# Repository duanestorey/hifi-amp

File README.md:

# hifi-amp
A hi-fi 4-channel amplifier with active-crossovers and room correction

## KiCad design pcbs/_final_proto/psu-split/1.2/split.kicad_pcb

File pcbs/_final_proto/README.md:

## Next Updates

* Opamp voltage regulator has enable pin - can use that to kill the rails instead of a relay on split board
* Change vinyl to Muffy
* See if we can move relay for LM3886 rails somewhere else
* Add LPF to opamp power supply caps, possibly digital too

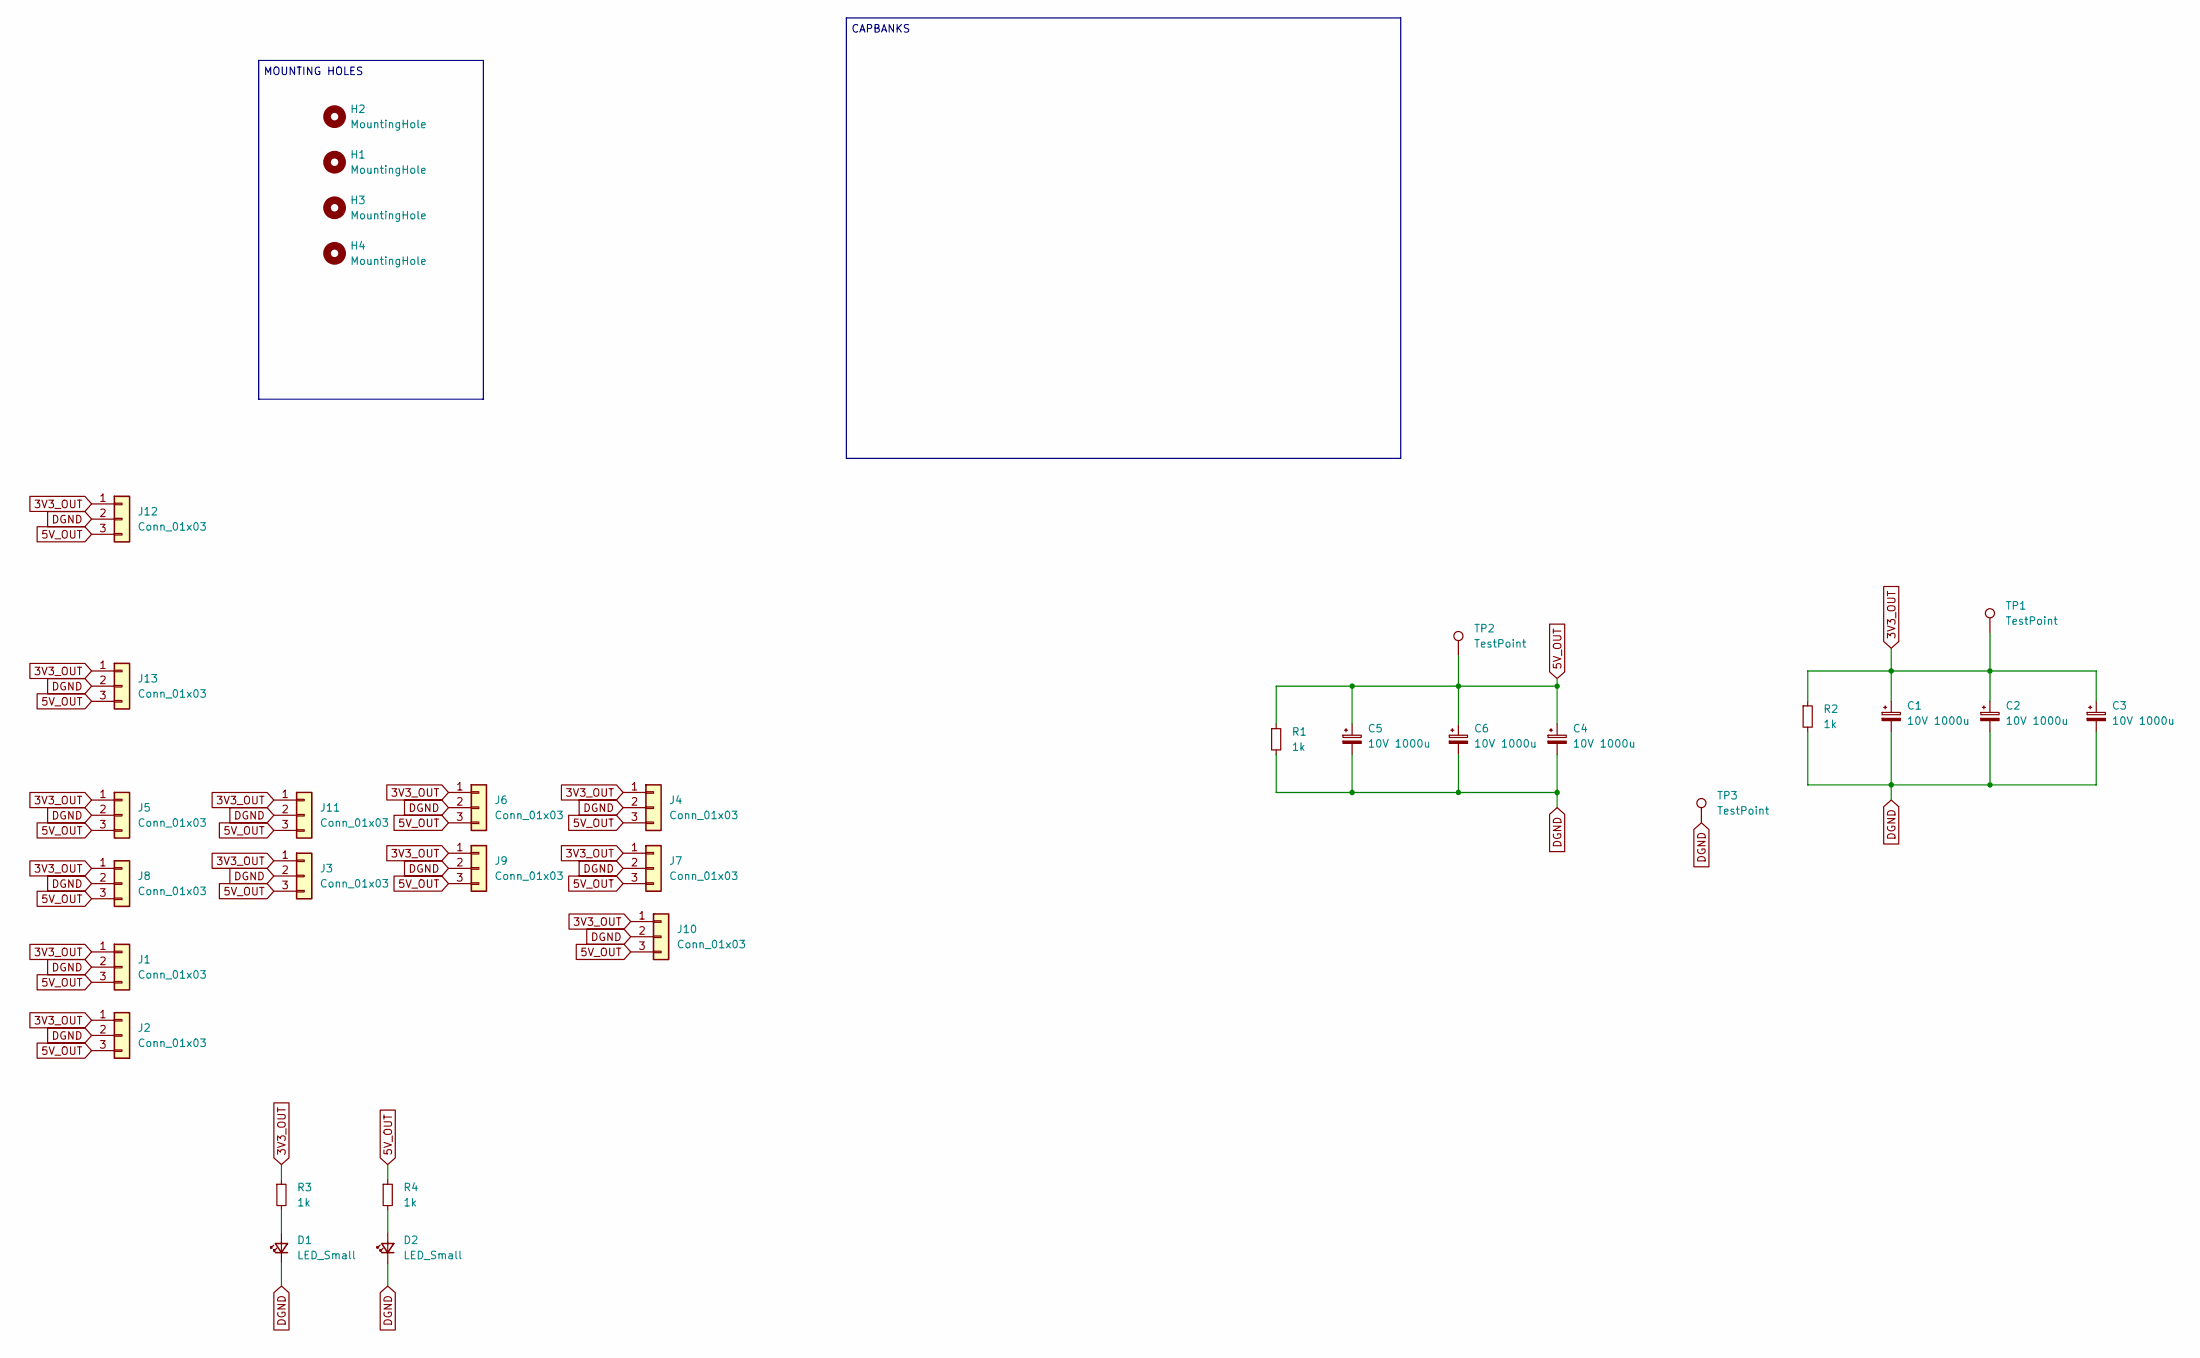
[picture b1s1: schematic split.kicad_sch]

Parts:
C1, C2, C3, C4, C5, C6: 10V 1000u; CP_Elec_10x10
D1, D2: LED_Small; LED_0805_2012Metric_Pad_HandSolder_Duane
H1, H2, H3, H4: MountingHole; MountingHole_3.2mm_M3_DIN965_Pad_TopBottom
J1, J2, J3, J4, J5, J6, J7, J8, J9, J10, J11, J13: Conn_01x03; JST_PH_B3B-PH-K_1x03_P2.00mm_Vertical
J12: Conn_01x03; JST_VH_B3P-VH-B_1x03_P3.96mm_Vertical_Duane
R1, R2, R3, R4: 1k; R_0805_2012Metric_Pad1.20x1.40mm_HandSolder_Duane
TP1, TP2, TP3: TestPoint; TestPoint_THTPad_2.5x2.5mm_Drill1.2mm

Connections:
3V3_OUT: C1.1, C2.1, C3.1, J1.1, J2.1, J3.1, J4.1, J5.1, J6.1, J7.1, J8.1, J9.1, J10.1, J11.1, J12.1, J13.1, R2.1, R3.1, TP1.1
5V_OUT: C4.1, C5.1, C6.1, J1.3, J2.3, J3.3, J4.3, J5.3, J6.3, J7.3, J8.3, J9.3, J10.3, J11.3, J12.3, J13.3, R1.1, R4.1, TP2.1
DGND: C1.2, C2.2, C3.2, C4.2, C5.2, C6.2, D1.1 (K), D2.1 (K), J1.2, J2.2, J3.2, J4.2, J5.2, J6.2, J7.2, J8.2, J9.2, J10.2, J11.2, J12.2, J13.2, R1.2, R2.2, TP3.1
unnamed: D1.2 (A), R3.2
unnamed: D2.2 (A), R4.2

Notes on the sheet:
MOUNTING HOLES
CAPBANKS

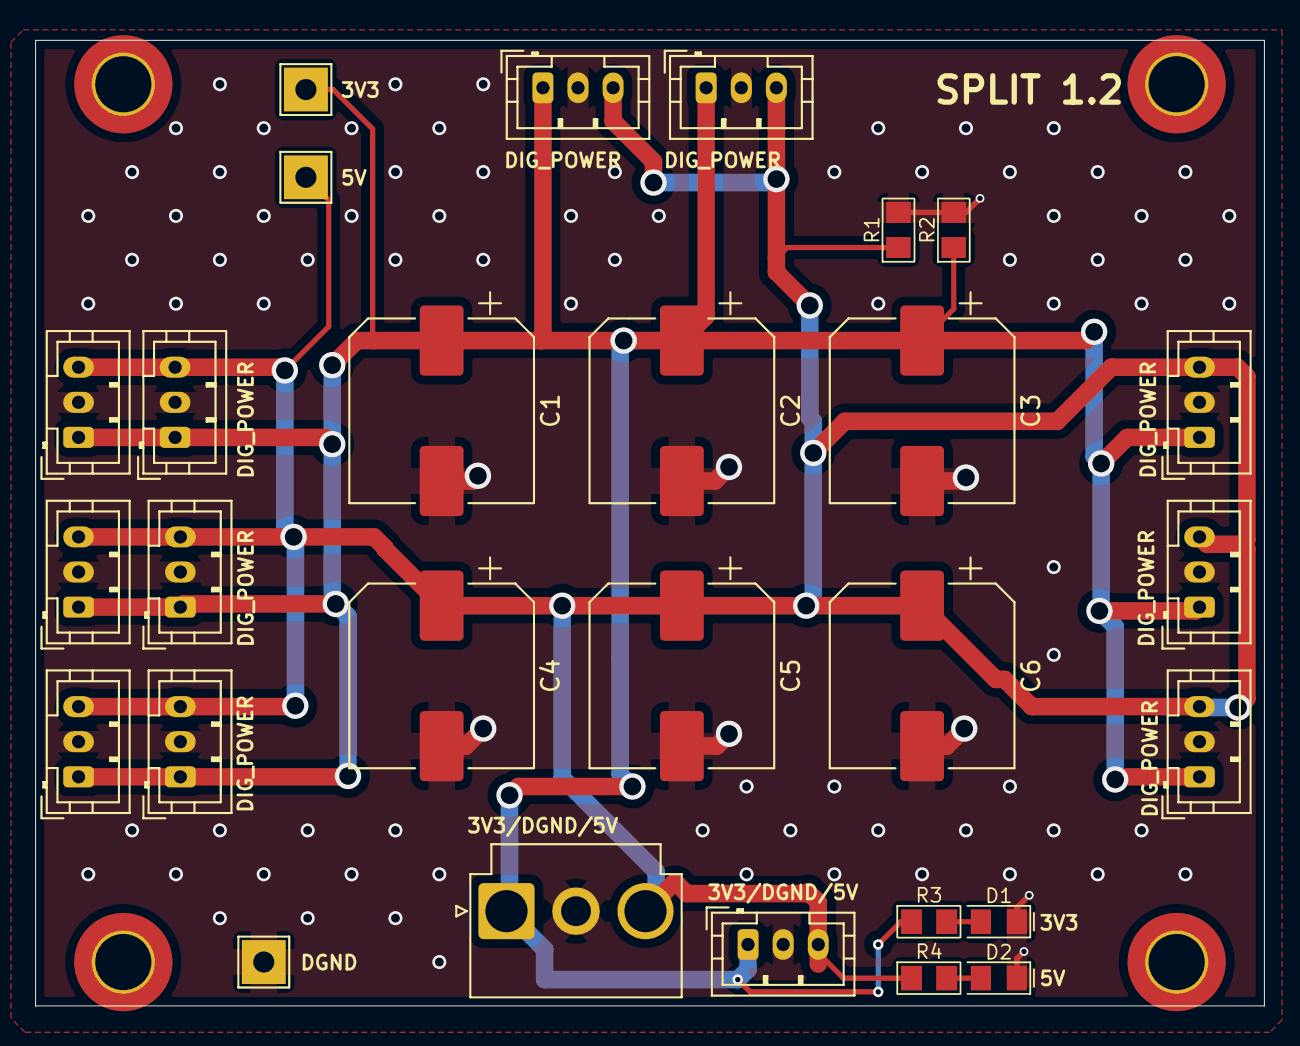
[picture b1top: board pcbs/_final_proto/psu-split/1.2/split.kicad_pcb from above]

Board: 2 copper layers, 70.0 x 55.0 mm, 32 parts (0 on the bottom side), 5 nets.

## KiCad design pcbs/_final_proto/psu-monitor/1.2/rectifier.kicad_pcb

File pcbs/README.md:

## Printed Circuit Boards

These are all the associated PCBs for the amplifier project.  They were all created in Kicad, and the boards optimized for production via JLCPCB.

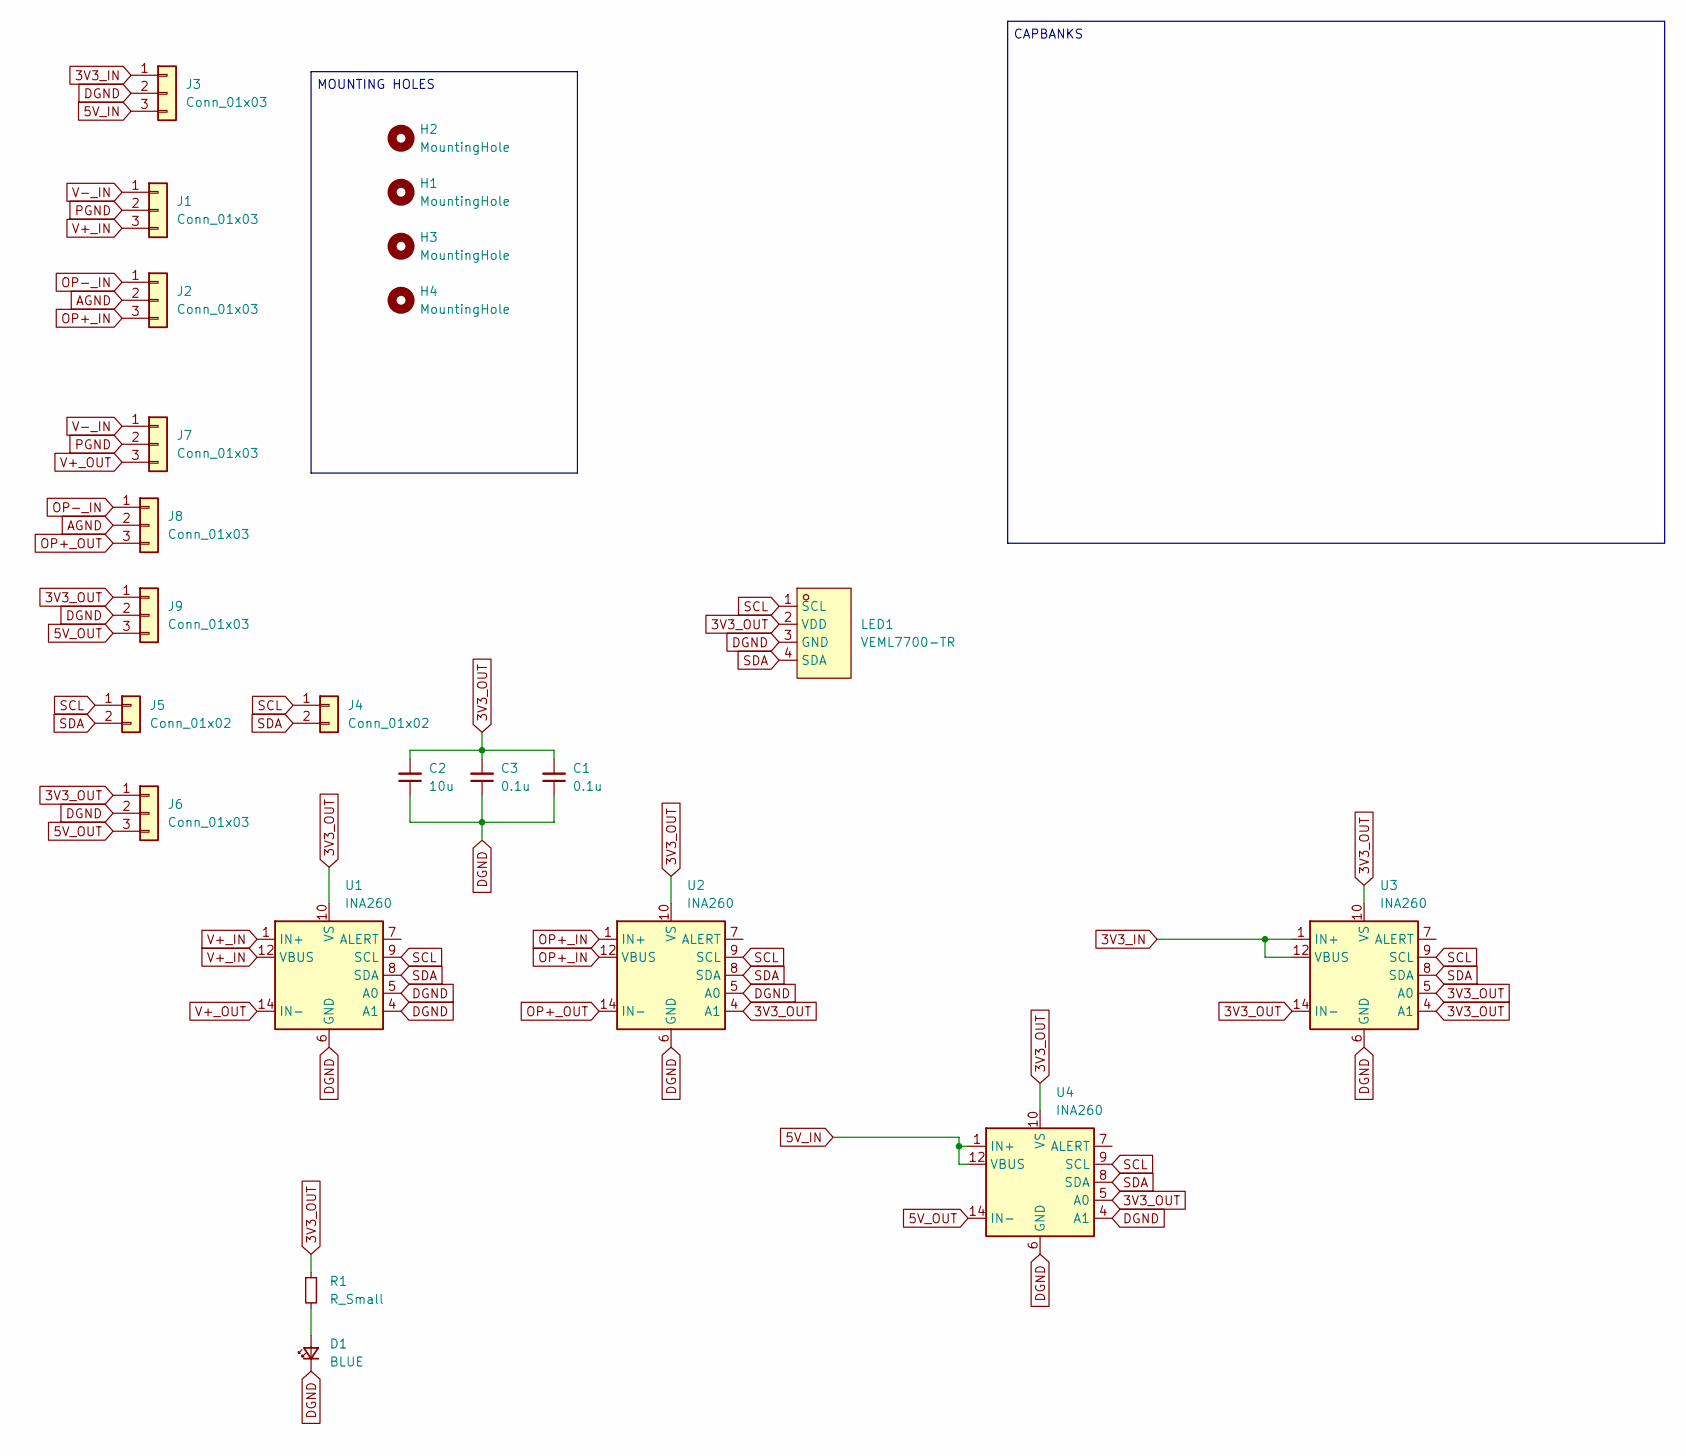
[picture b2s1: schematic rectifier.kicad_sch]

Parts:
C1, C3: 0.1u; C_0805_2012Metric_Pad1.18x1.45mm_HandSolder_Duane
C2: 10u; C_1206_3216Metric_Pad1.33x1.80mm_HandSolder_Duane
D1: BLUE; LED_0805_2012Metric_Pad_HandSolder_Duane
H1, H2, H3, H4: MountingHole; MountingHole_3.2mm_M3_DIN965_Pad_TopBottom
J1, J2, J3, J7, J8, J9: Conn_01x03; JST_VH_B3P-VH-B_1x03_P3.96mm_Vertical_Duane
J4, J5: Conn_01x02; JST_PH_B2B-PH-K_1x02_P2.00mm_Vertical
J6: Conn_01x03; JST_PH_B3B-PH-K_1x03_P2.00mm_Vertical
LED1: VEML7700-TR; LED-SMD_4P-L6.8-W2.4_VEML7700-TR; LCSC Part C504893
R1: R_Small; R_0805_2012Metric_Pad1.20x1.40mm_HandSolder_Duane
U1, U2, U3, U4: INA260; TSSOP-16_4.4x5mm_P0.65mm

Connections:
3V3_IN: J3.1, U3.1 (IN+), U3.2 (IN+), U3.3 (IN+), U3.12 (VBUS)
3V3_OUT: C1.2, C2.2, C3.2, J6.1, J9.1, LED1.2 (VDD), R1.1, U1.10 (VS), U2.4 (A1), U2.10 (VS), U3.4 (A1), U3.5 (A0), U3.10 (VS), U3.14 (IN-), U3.15 (IN-), U3.16 (IN-), U4.5 (A0), U4.10 (VS)
5V_IN: J3.3, U4.1 (IN+), U4.2 (IN+), U4.3 (IN+), U4.12 (VBUS)
5V_OUT: J6.3, J9.3, U4.14 (IN-), U4.15 (IN-), U4.16 (IN-)
AGND: J2.2, J8.2
DGND: C1.1, C2.1, C3.1, D1.1 (K), J3.2, J6.2, J9.2, LED1.3 (GND), U1.4 (A1), U1.5 (A0), U1.6 (GND), U1.11 (GND), U2.5 (A0), U2.6 (GND), U2.11 (GND), U3.6 (GND), U3.11 (GND), U4.4 (A1), U4.6 (GND), U4.11 (GND)
unnamed: D1.2 (A), R1.2
OP+_IN: J2.3, U2.1 (IN+), U2.2 (IN+), U2.3 (IN+), U2.12 (VBUS)
OP+_OUT: J8.3, U2.14 (IN-), U2.15 (IN-), U2.16 (IN-)
OP-_IN: J2.1, J8.1
PGND: J1.2, J7.2
SCL: J4.1, J5.1, LED1.1 (SCL), U1.9 (SCL), U2.9 (SCL), U3.9 (SCL), U4.9 (SCL)
SDA: J4.2, J5.2, LED1.4 (SDA), U1.8 (SDA), U2.8 (SDA), U3.8 (SDA), U4.8 (SDA)
V+_IN: J1.3, U1.1 (IN+), U1.2 (IN+), U1.3 (IN+), U1.12 (VBUS)
V+_OUT: J7.3, U1.14 (IN-), U1.15 (IN-), U1.16 (IN-)
V-_IN: J1.1, J7.1

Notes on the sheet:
MOUNTING HOLES
CAPBANKS

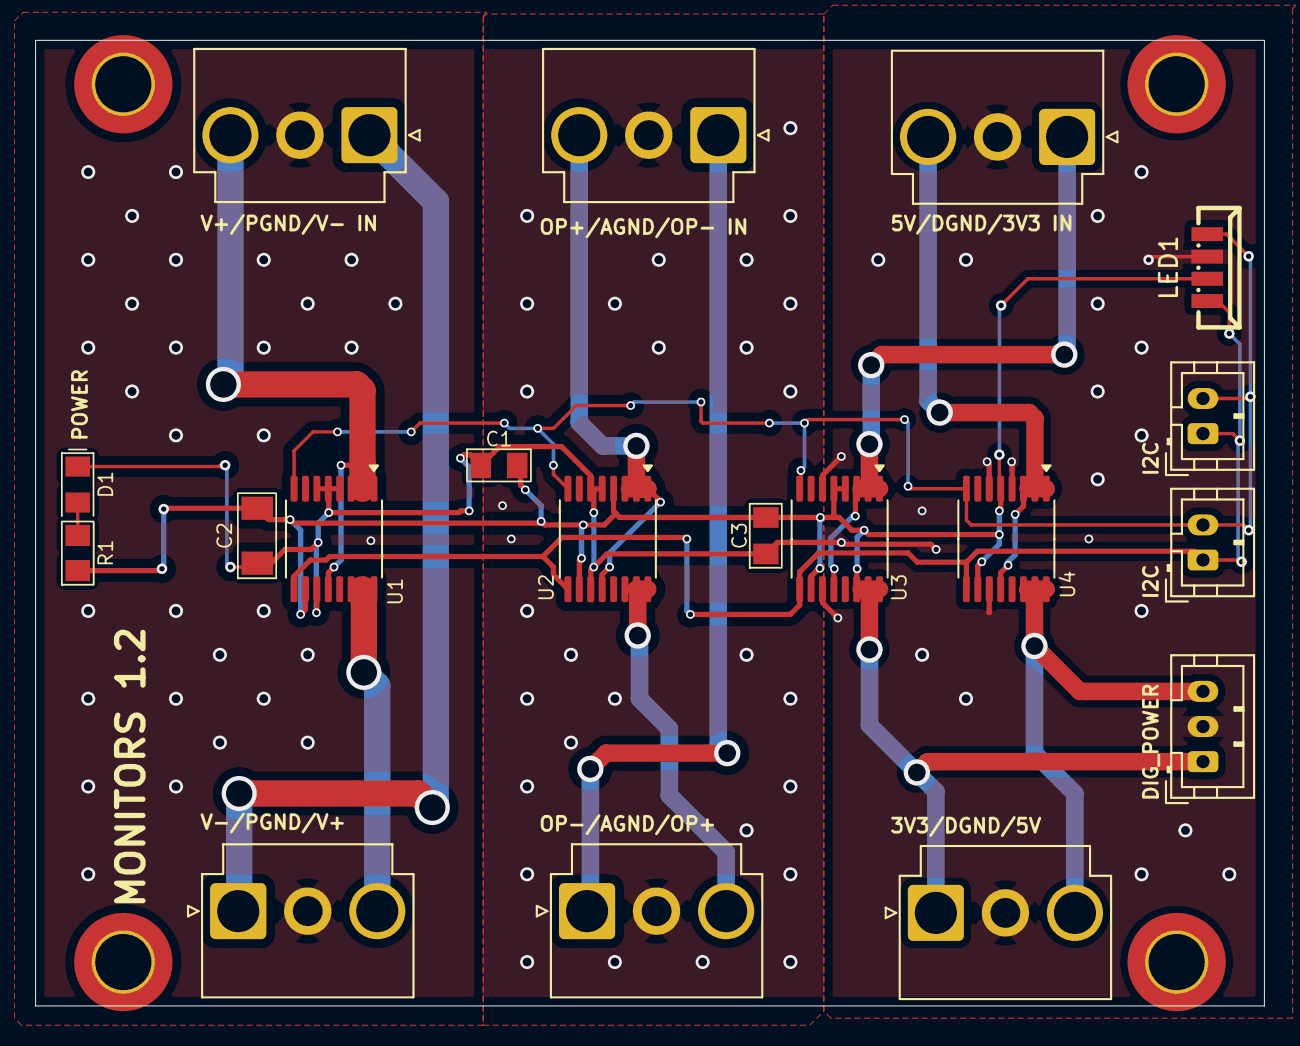
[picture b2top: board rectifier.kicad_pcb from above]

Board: 2 copper layers, 70.0 x 55.0 mm, 23 parts (0 on the bottom side), 16 nets.

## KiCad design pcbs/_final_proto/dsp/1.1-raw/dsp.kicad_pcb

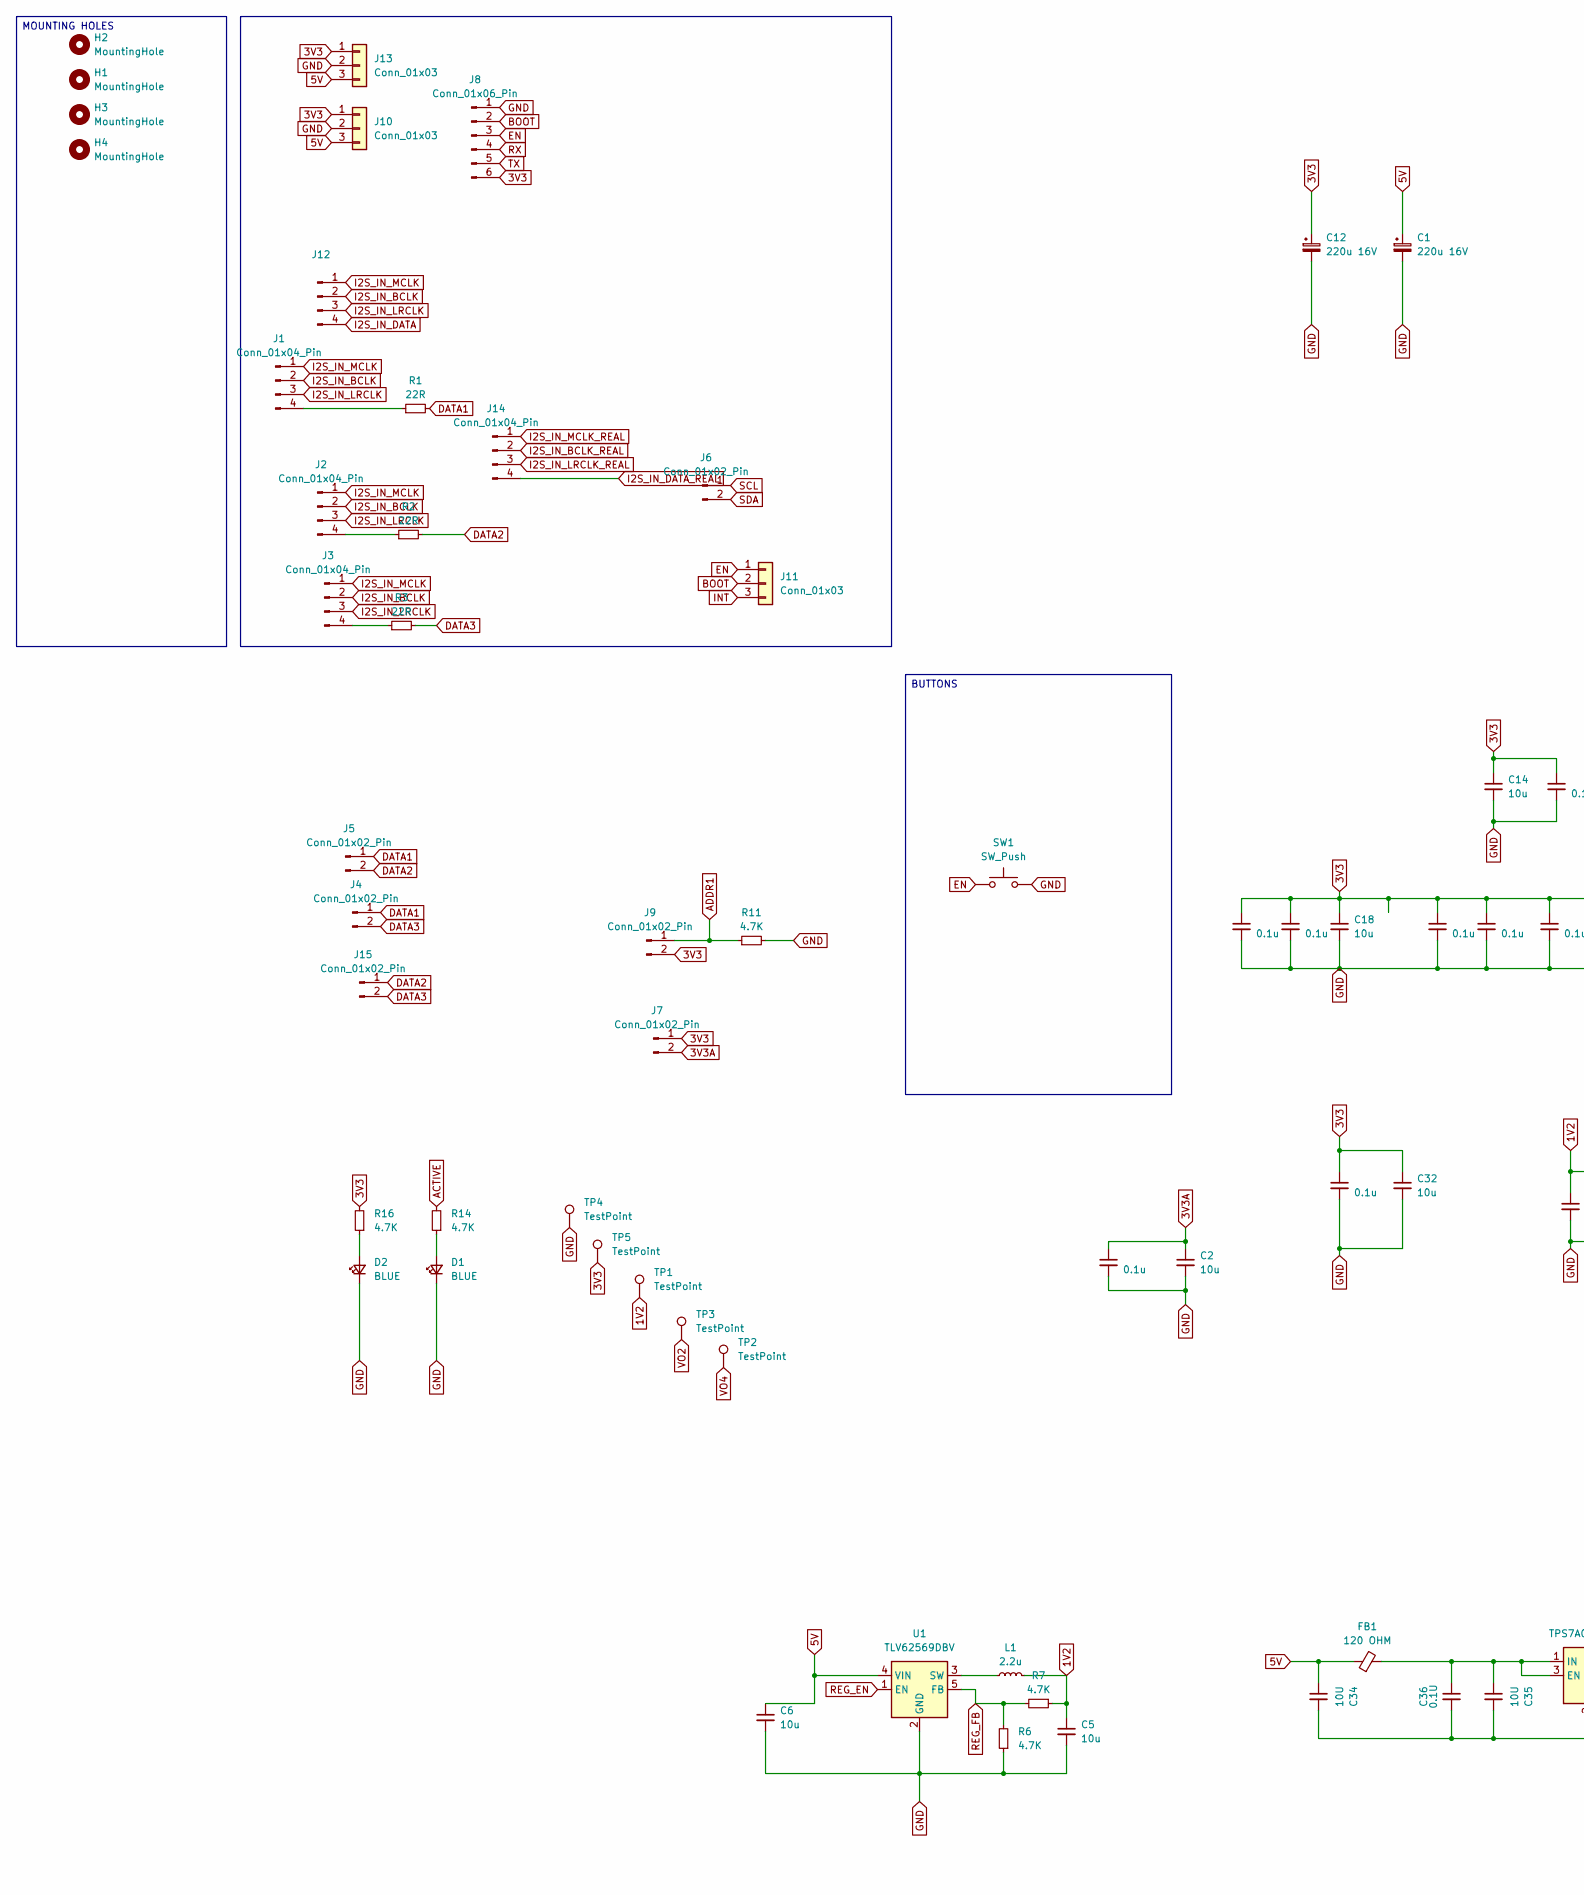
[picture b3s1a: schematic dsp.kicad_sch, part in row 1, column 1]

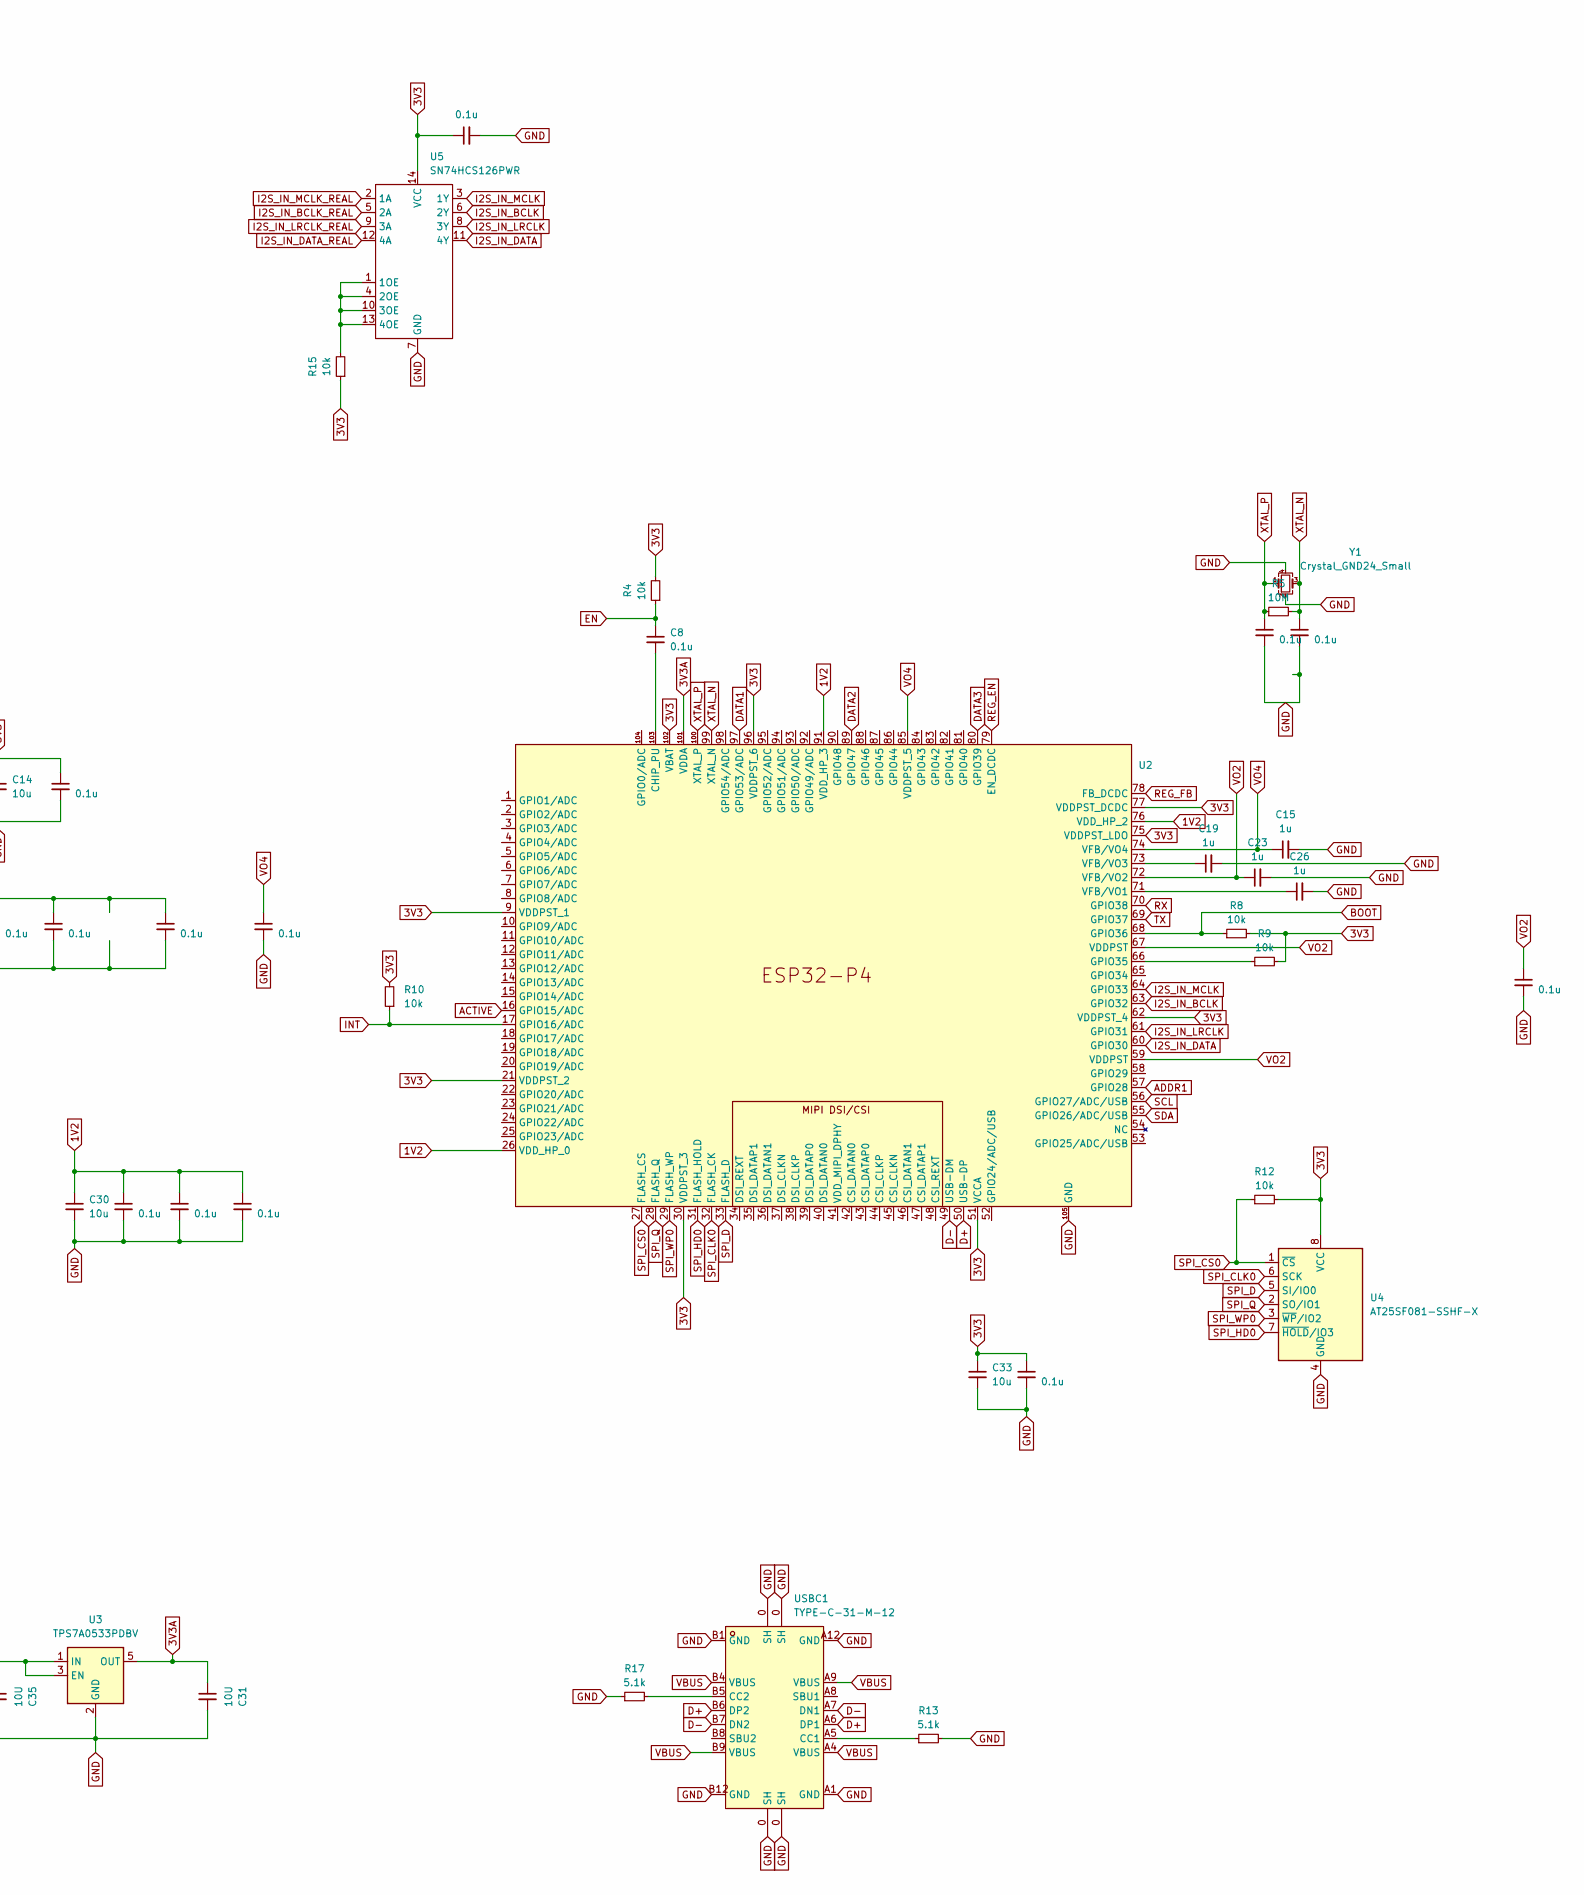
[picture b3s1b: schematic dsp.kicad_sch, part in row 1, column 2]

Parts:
C1, C12: 220u 16V; CP_Elec_6.3x7.7
C2, C5, C6, C14, C18, C30, C32, C33: 10u; C_1206_3216Metric_Pad1.33x1.80mm_HandSolder
C3, C4, C7, C8, C9, C10, C11, C13, C16, C17, C20, C21, C22, C24, C25, C27, C28, C29, C37: 0.1u; C_0805_2012Metric_Pad1.18x1.45mm_HandSolder
C15, C19, C23, C26: 1u; C_1206_3216Metric_Pad1.33x1.80mm_HandSolder
C31, C34, C35: 10U; C_1206_3216Metric_Pad1.33x1.80mm_HandSolder
C36: 0.1U; C_0805_2012Metric_Pad1.18x1.45mm_HandSolder
D1, D2: BLUE; LED_0805_2012Metric_Pad_HandSolder_Duane
FB1: 120 OHM; R_0603_1608Metric_Pad0.98x0.95mm_HandSolder
H1, H2, H3, H4: MountingHole; MountingHole_3.2mm_M3_DIN965_Pad_TopOnly
J1, J2, J3, J14: Conn_01x04_Pin; JST_PH_B4B-PH-K_1x04_P2.00mm_Vertical
J4, J5, J7, J9, J15: Conn_01x02_Pin; PinHeader_1x02_P2.54mm_Vertical
J6: Conn_01x02_Pin; JST_PH_B2B-PH-K_1x02_P2.00mm_Vertical
J8: Conn_01x06_Pin; PinHeader_1x06_P2.54mm_Vertical
J10, J11, J13: Conn_01x03; JST_PH_B3B-PH-K_1x03_P2.00mm_Vertical
J12: Conn_01x04_Pin; PinHeader_1x04_P2.54mm_Vertical
L1: 2.2u; L_0805_2012Metric_Pad1.15x1.40mm_HandSolder
R1, R2, R3: 22R; R_0805_2012Metric_Pad1.20x1.40mm_HandSolder; LCSC C23162
R4, R8, R9, R10, R12, R15: 10k; R_0805_2012Metric_Pad1.20x1.40mm_HandSolder; Mouser 603-RT0805FRE0722RL
R5: 10M; R_0805_2012Metric_Pad1.20x1.40mm_HandSolder; Mouser 603-RT0805FRE0722RL
R6, R7, R11, R14, R16: 4.7K; R_0805_2012Metric_Pad1.20x1.40mm_HandSolder; LCSC C23162
R13, R17: 5.1k; R_0805_2012Metric_Pad1.20x1.40mm_HandSolder; Mouser 603-RT0805FRE0722RL
SW1: SW_Push; Button Aliexpress 4x4
TP1, TP2, TP3, TP4, TP5: TestPoint; TestPoint_THTPad_1.5x1.5mm_Drill0.7mm
U1: TLV62569DBV; SOT-23-5
U2: ESP32-P4
U3: TPS7A0533PDBV; SOT-23-5
U4: AT25SF081-SSHF-X; SOP-8_3.76x4.96mm_P1.27mm
U5: SN74HCS126PWR; TSSOP-14_4.4x5mm_P0.65mm; Mouser SN74HCS126PWR
USBC1: TYPE-C-31-M-12; USB-C_SMD-TYPE-C-31-M-12; LCSC Part C165948
Y1: Crystal_GND24_Small; Crystal_SMD_SeikoEpson_FA238-4Pin_3.2x2.5mm

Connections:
1V2: C5.1, C10.1, C17.1, C27.1, C30.1, L1.2, R7.1, TP1.1, U2.26 (VDD_HP_0), U2.76 (VDD_HP_2), U2.91 (VDD_HP_3)
3V3: C9.1, C12.1, C13.1, C14.1, C16.1, C18.1, C20.1, C21.1, C22.1, C24.1, C28.1, C29.1, C32.1, C33.1, C37.1, J7.1, J8.6, J9.2, J10.1, J13.1, R4.2, R8.2, R9.2, R10.2, R12.2, R15.1, R16.2, TP5.1, U2.9 (VDDPST_1), U2.21 (VDDPST_2), U2.30 (VDDPST_3), U2.51 (VCCA), U2.62 (VDDPST_4), U2.75 (VDDPST_LDO), U2.77 (VDDPST_DCDC), U2.96 (VDDPST_6), U2.102 (VBAT), U4.8 (VCC), U5.14 (VCC)
3V3A: C2.1, C7.1, C31.1, J7.2, U2.101 (VDDA), U3.5 (OUT)
5V: C1.1, C6.1, C34.1, FB1.1, J10.3, J13.3, U1.4 (VIN)
ACTIVE: R14.2, U2.16 (GPIO15/ADC)
ADDR1: J9.1, R11.1, U2.57 (GPIO28)
BOOT: J8.2, J11.2, R8.1, U2.68 (GPIO36)
D+: U2.50 (USB-DP), USBC1.A6 (DP1), USBC1.B6 (DP2)
D-: U2.49 (USB-DM), USBC1.A7 (DN1), USBC1.B7 (DN2)
DATA1: J4.1, J5.1, R1.2, U2.97 (GPIO53/ADC)
DATA2: J5.2, J15.1, R2.2, U2.89 (GPIO47)
DATA3: J4.2, J15.2, R3.2, U2.80 (GPIO39)
EN: C8.1, J8.3, J11.1, R4.1, SW1.1
GND: C1.2, C2.2, C3.2, C4.2, C5.2, C6.2, C7.2, C9.2, C10.2, C11.2, C12.2, C13.2, C14.2, C15.2, C16.2, C17.2, C18.2, C19.2, C20.2, C21.2, C22.2, C23.2, C24.2, C25.2, C26.2, C27.2, C28.2, C29.2, C30.2, C31.2, C32.2, C33.2, C34.2, C35.2, C36.2, C37.2, D1.1 (K), D2.1 (K), J8.1, J10.2, J13.2, R6.1, R11.2, R13.2, R17.1, SW1.2, TP4.1, U1.2 (GND), U2.105 (GND), U3.2 (GND), U4.4 (GND), U5.7 (GND), USBC1.0 (SH), USBC1.A1 (GND), USBC1.A12 (GND), USBC1.B1 (GND), USBC1.B12 (GND), Y1.2, Y1.4
I2S_IN_BCLK: J1.2, J2.2, J3.2, J12.2, U2.63 (GPIO32), U5.6 (2Y)
I2S_IN_BCLK_REAL: J14.2, U5.5 (2A)
I2S_IN_DATA: J12.4, U2.60 (GPIO30), U5.11 (4Y)
I2S_IN_DATA_REAL: J14.4, U5.12 (4A)
I2S_IN_LRCLK: J1.3, J2.3, J3.3, J12.3, U2.61 (GPIO31), U5.8 (3Y)
I2S_IN_LRCLK_REAL: J14.3, U5.9 (3A)
I2S_IN_MCLK: J1.1, J2.1, J3.1, J12.1, U2.64 (GPIO33), U5.3 (1Y)
I2S_IN_MCLK_REAL: J14.1, U5.2 (1A)
INT: J11.3, R10.1, U2.17 (GPIO16/ADC)
unnamed: D1.2 (A), R14.1
unnamed: D2.2 (A), R16.1
unnamed: J1.4, R1.1
unnamed: J2.4, R2.1
unnamed: J3.4, R3.1
unnamed: L1.1, U1.3 (SW)
unnamed: C8.2, U2.103 (CHIP_PU)
unnamed: R9.1, U2.66 (GPIO35)
unnamed: C26.1, U2.71 (VFB/VO1)
unnamed: C19.1, U2.73 (VFB/VO3)
unnamed: C35.1, C36.1, FB1.2, U3.1 (IN), U3.3 (EN)
unnamed: R15.2, U5.1 (1OE), U5.4 (2OE), U5.10 (3OE), U5.13 (4OE)
unnamed: R13.1, USBC1.A5 (CC1)
unnamed: R17.2, USBC1.B5 (CC2)
REG_EN: U1.1 (EN), U2.79 (EN_DCDC)
REG_FB: R6.2, R7.2, U1.5 (FB), U2.78 (FB_DCDC)
RX: J8.4, U2.70 (GPIO38)
SCL: J6.1, U2.56 (GPIO27/ADC/USB)
SDA: J6.2, U2.55 (GPIO26/ADC/USB)
SPI_CLK0: U2.32 (FLASH_CK), U4.6 (SCK)
SPI_CS0: R12.1, U2.27 (FLASH_CS), U4.1 (~CS)
SPI_D: U2.33 (FLASH_D), U4.5 (SI/IO0)
SPI_HD0: U2.31 (FLASH_HOLD), U4.7 (~HOLD/IO3)
SPI_Q: U2.28 (FLASH_Q), U4.2 (SO/IO1)
SPI_WP0: U2.29 (FLASH_WP), U4.3 (~WP/IO2)
TX: J8.5, U2.69 (GPIO37)
VBUS: USBC1.A4 (VBUS), USBC1.A9 (VBUS), USBC1.B4 (VBUS), USBC1.B9 (VBUS)
VO2: C23.1, C25.1, TP3.1, U2.59 (VDDPST), U2.67 (VDDPST), U2.72 (VFB/VO2)
VO4: C11.1, C15.1, TP2.1, U2.74 (VFB/VO4), U2.85 (VDDPST_5)
XTAL_N: C4.1, R5.2, U2.99 (XTAL_N), Y1.3
XTAL_P: C3.1, R5.1, U2.100 (XTAL_P), Y1.1

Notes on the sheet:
MOUNTING HOLES
BUTTONS

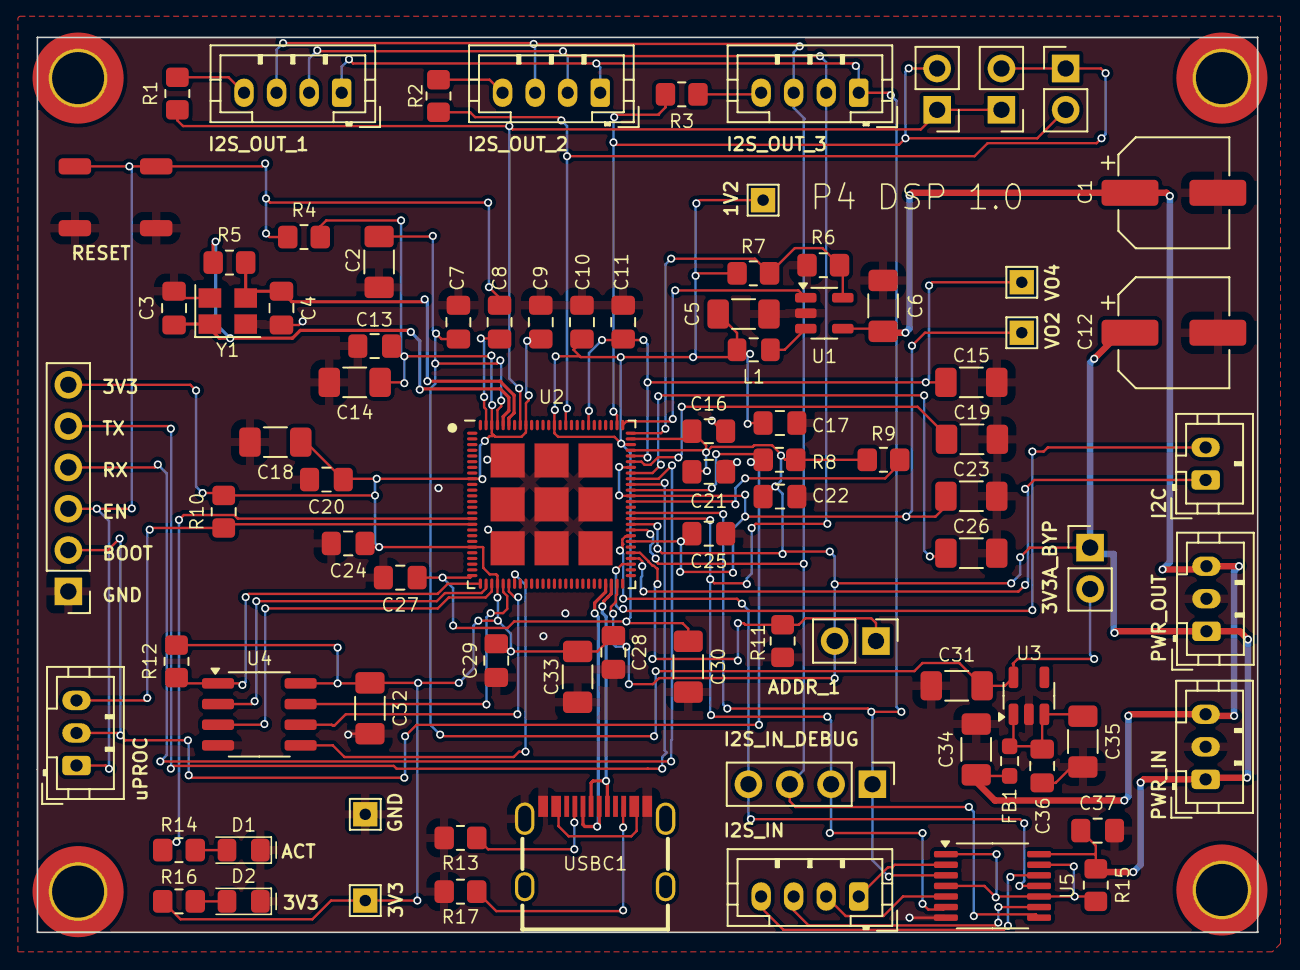
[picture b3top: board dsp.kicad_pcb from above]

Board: 2 copper layers, 75.0 x 55.0 mm, 90 parts (0 on the bottom side), 54 nets.
